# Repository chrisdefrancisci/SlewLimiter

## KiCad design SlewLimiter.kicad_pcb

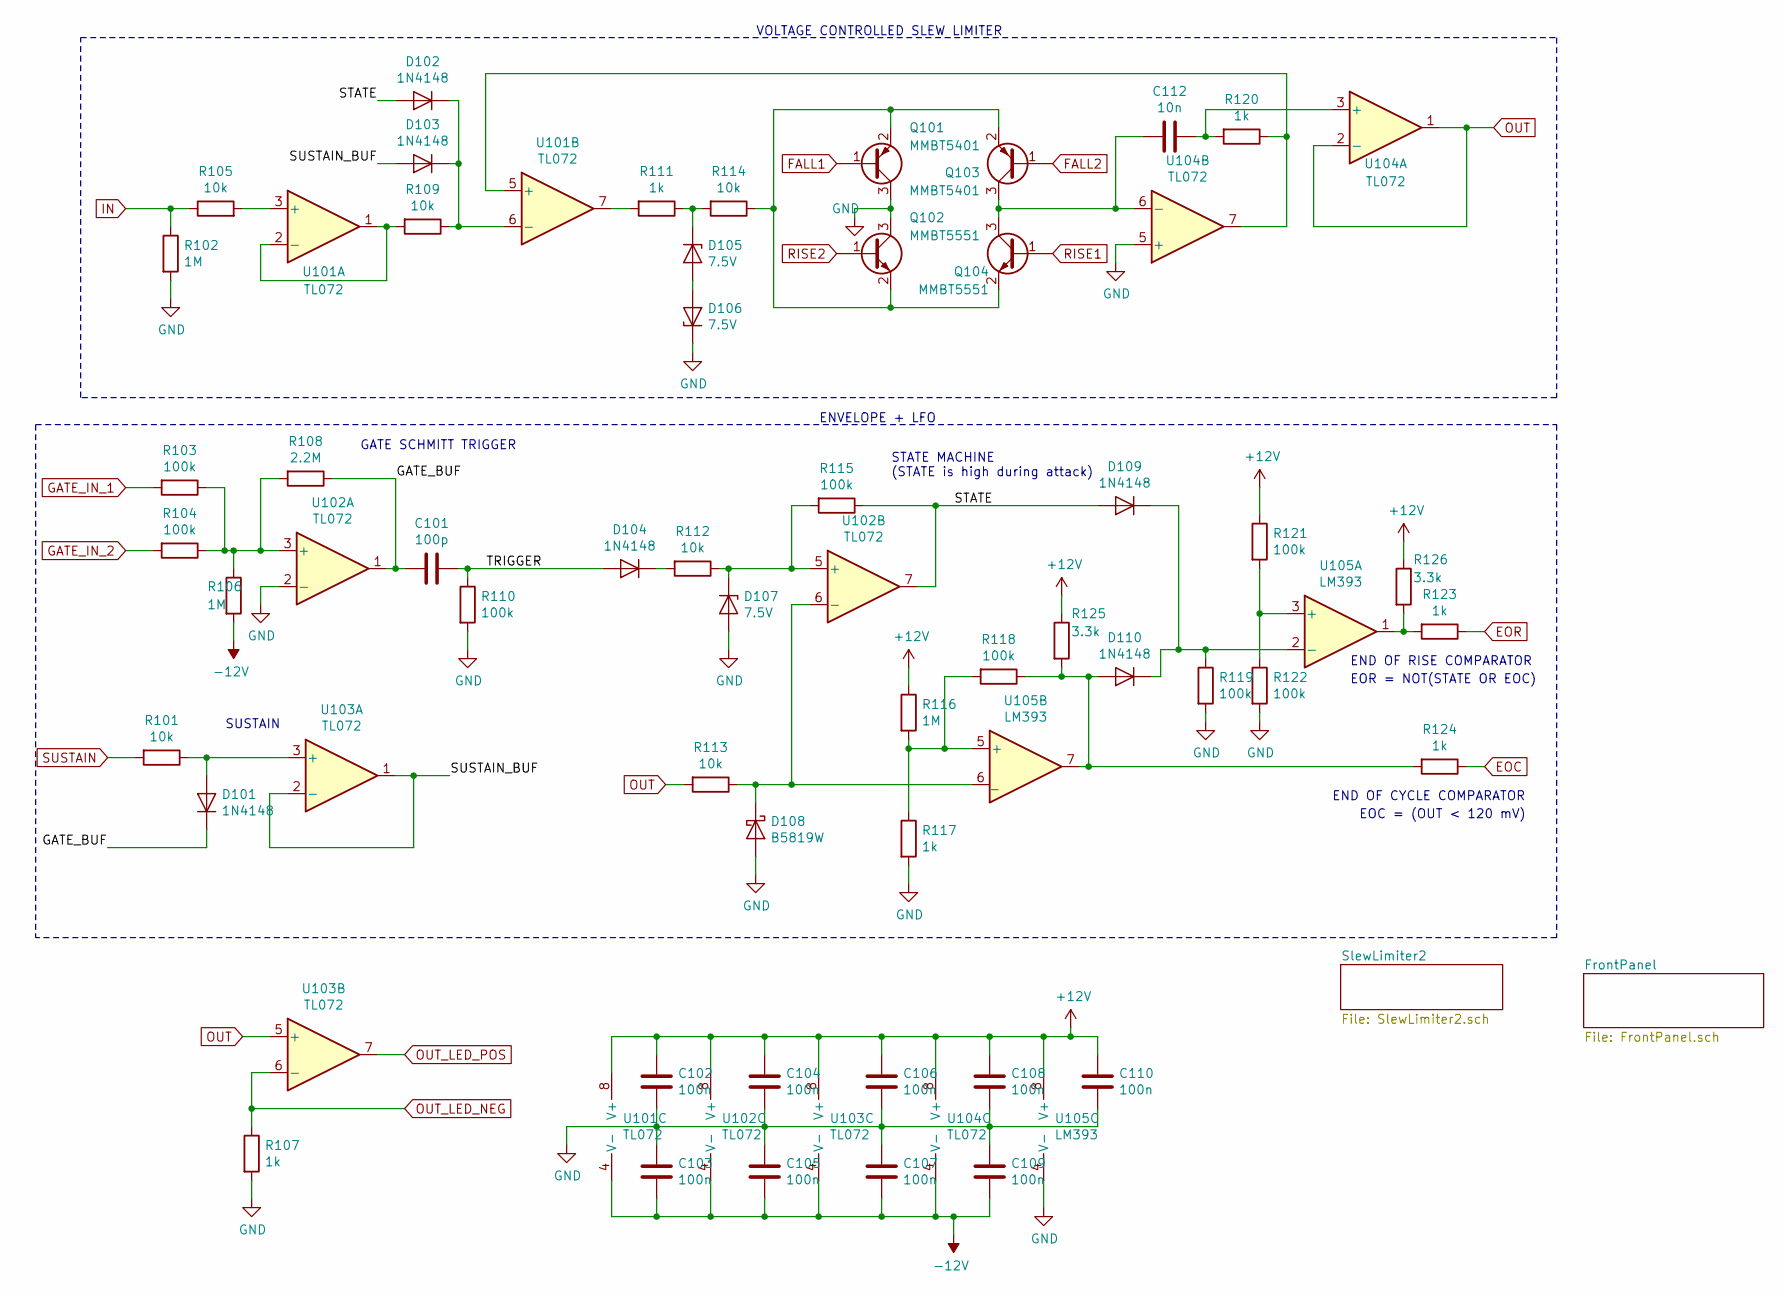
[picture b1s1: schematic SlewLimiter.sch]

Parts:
C101: 100p; C_0402_1005Metric; LCSC C1546
C102, C103, C104, C105, C106, C107, C108, C109, C110: 100n; C_0402_1005Metric; LCSC C1525
C112: 10n; C_0402_1005Metric; LCSC C15195
D101, D102, D103, D104, D109, D110: 1N4148; D_SOD-323F; LCSC C2128
D105, D106, D107: 7.5V; D_DO-35_SOD27_P7.62mm_Horizontal
D108: B5819W; D_SOD-123; LCSC C8598
Q101, Q103: MMBT5401; SOT-23; LCSC C8326
Q102, Q104: MMBT5551; SOT-23; LCSC C2145
R101, R105, R109, R112, R113, R114: 10k; R_0402_1005Metric; LCSC C25744
R102, R106, R116: 1M; R_0402_1005Metric; LCSC C26083
R103, R104, R110, R115, R118, R119, R121, R122: 100k; R_0402_1005Metric; LCSC C25741
R107, R111, R117, R120, R123, R124: 1k; R_0402_1005Metric; LCSC C11702
R108: 2.2M; R_0402_1005Metric; LCSC C11490
R125, R126: 3.3k; R_0402_1005Metric; LCSC C25890
U101, U102, U103, U104: TL072; SOIC-8_3.9x4.9mm_P1.27mm; LCSC C6961
U105: LM393; SOIC-8_3.9x4.9mm_P1.27mm; LCSC C7955

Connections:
+12V: C102.1, C104.1, C106.1, C108.1, C110.1, R116.1, R121.1, R125.1, R126.1, U101.8 (V+), U102.8 (V+), U103.8 (V+), U104.8 (V+), U105.8 (V+); also elsewhere on the board
-12V: C103.2, C105.2, C107.2, C109.2, R106.2, U101.4 (V-), U102.4 (V-), U103.4 (V-), U104.4 (V-); also elsewhere on the board
/GATE_BUF: C101.2, D101.1 (K), R108.1, U102.1
/STATE: D102.2 (A), D109.2 (A), R115.1, U102.7
/SUSTAIN_BUF: D103.2 (A), U103.1, U103.2 (-)
/TRIGGER: C101.1, D104.2 (A), R110.1
EOC: R124.1; also elsewhere on the board
EOR: R123.1; also elsewhere on the board
FALL1: Q101.1 (B); also elsewhere on the board
FALL2: Q103.1 (B); also elsewhere on the board
GATE_IN_1: R103.2; also elsewhere on the board
GATE_IN_2: R104.2; also elsewhere on the board
GND: C102.2, C103.1, C104.2, C105.1, C106.2, C107.1, C108.2, C109.1, C110.2, D106.1 (K), D107.2 (A), D108.2 (A), Q101.3 (C), Q102.3 (C), R102.2, R107.2, R110.2, R117.2, R119.2, R122.2, U102.2 (-), U104.5 (+), U105.4 (V-); also elsewhere on the board
IN: R102.1, R105.1; also elsewhere on the board
unnamed: C112.1, R120.2, U104.3 (+)
unnamed: C112.2, Q103.3 (C), Q104.3 (C), U104.6 (-)
unnamed: D101.2 (A), R101.1, U103.3 (+)
unnamed: D102.1 (K), D103.1 (K), R109.1, U101.6 (-)
unnamed: D104.1 (K), R112.2
unnamed: D105.1 (K), R111.1, R114.2
unnamed: D105.2 (A), D106.2 (A)
unnamed: D107.1 (K), R112.1, R115.2, U102.5 (+)
unnamed: D108.1 (K), R113.1, U102.6 (-), U105.6 (_)
unnamed: D109.1 (K), D110.1 (K), R119.1, U105.2 (-)
unnamed: D110.2 (A), R118.1, R124.2, R125.2, U105.7
unnamed: Q101.2 (E), Q102.2 (E), Q103.2 (E), Q104.2 (E), R114.1
unnamed: R103.1, R104.1, R106.1, R108.2, U102.3 (+)
unnamed: R105.2, U101.3 (+)
unnamed: R109.2, U101.1, U101.2 (-)
unnamed: R111.2, U101.7
unnamed: R116.2, R117.1, R118.2, U105.5 (+)
unnamed: R120.1, U101.5 (+), U104.7
unnamed: R121.2, R122.1, U105.3 (+)
unnamed: R123.2, R126.2, U105.1
OUT: R113.2, U103.5 (+), U104.1, U104.2 (-); also elsewhere on the board
OUT_LED_NEG: R107.1, U103.6 (-); also elsewhere on the board
OUT_LED_POS: U103.7; also elsewhere on the board
RISE1: Q104.1 (B); also elsewhere on the board
RISE2: Q102.1 (B); also elsewhere on the board
SUSTAIN: R101.2; also elsewhere on the board

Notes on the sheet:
VOLTAGE CONTROLLED SLEW LIMITER
ENVELOPE + LFO
SUSTAIN
GATE SCHMITT TRIGGER
STATE MACHINE (STATE is high during attack)
END OF CYCLE COMPARATOR
END OF RISE COMPARATOR
EOC = (OUT < 120 mV)
EOR = NOT(STATE OR EOC)

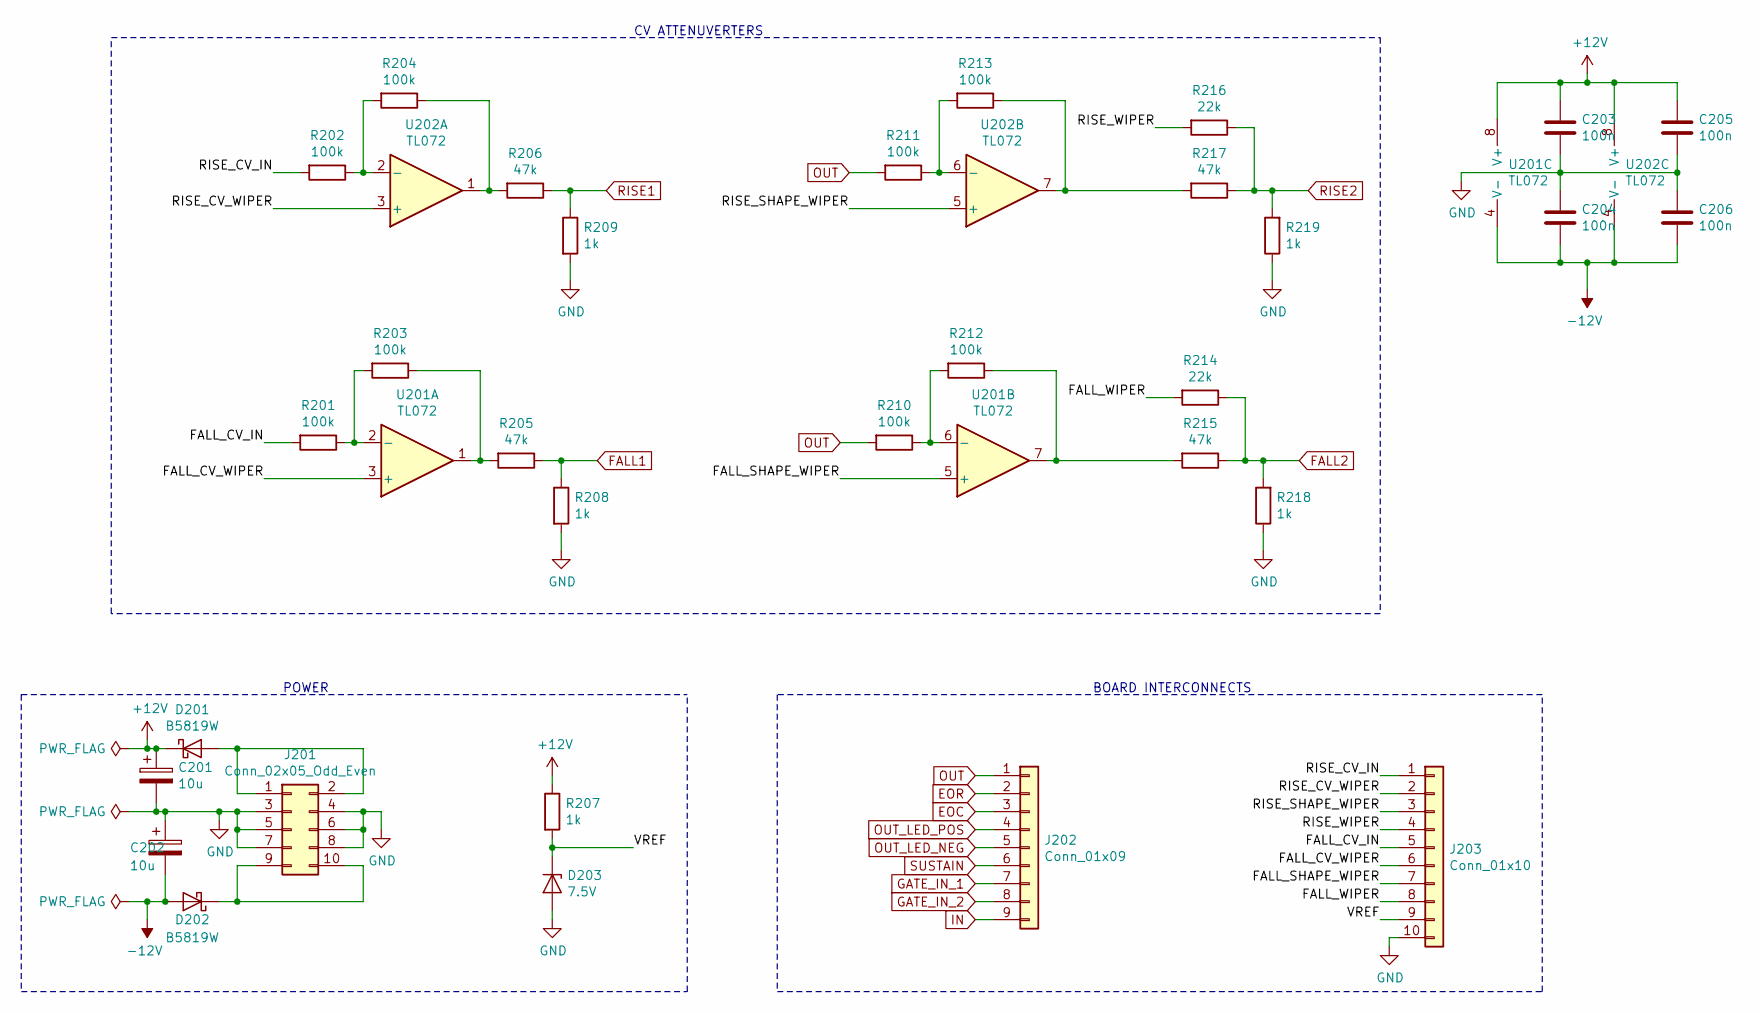
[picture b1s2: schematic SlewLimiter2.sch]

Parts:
C201, C202: 10u; C_0402_1005Metric; LCSC C15525
C203, C204, C205, C206: 100n; C_0402_1005Metric; LCSC C1525
D201, D202: B5819W; D_SOD-123; LCSC C8598
D203: 7.5V; D_DO-35_SOD27_P7.62mm_Horizontal
J201: Conn_02x05_Odd_Even; PinHeader_2x05_P2.54mm_Vertical
J202: Conn_01x09; PinHeader_1x09_P2.54mm_Vertical
J203: Conn_01x10; PinHeader_1x10_P2.54mm_Vertical
R201, R202, R203, R204, R210, R211, R212, R213: 100k; R_0402_1005Metric; LCSC C25741
R205, R206, R215, R217: 47k; R_0402_1005Metric; LCSC C25792
R207, R208, R209, R218, R219: 1k; R_0402_1005Metric; LCSC C11702
R214, R216: 22k; R_0402_1005Metric; LCSC C25768
U201, U202: TL072; SOIC-8_3.9x4.9mm_P1.27mm; LCSC C6961

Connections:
+12V: C201.1, C203.1, C205.1, D201.1 (K), R207.1, U201.8 (V+), U202.8 (V+); also elsewhere on the board
-12V: C202.2, C204.2, C206.2, D202.2 (A), U201.4 (V-), U202.4 (V-); also elsewhere on the board
/SlewLimiter2/FALL_CV_IN: J203.5, R201.2
/SlewLimiter2/FALL_CV_WIPER: J203.6, U201.3 (+)
/SlewLimiter2/FALL_SHAPE_WIPER: J203.7, U201.5 (+)
/SlewLimiter2/FALL_WIPER: J203.8, R214.2
/SlewLimiter2/RISE_CV_IN: J203.1, R202.2
/SlewLimiter2/RISE_CV_WIPER: J203.2, U202.3 (+)
/SlewLimiter2/RISE_SHAPE_WIPER: J203.3, U202.5 (+)
/SlewLimiter2/RISE_WIPER: J203.4, R216.2
/SlewLimiter2/VREF: D203.1 (K), J203.9, R207.2
EOC: J202.3; also elsewhere on the board
EOR: J202.2; also elsewhere on the board
FALL1: R205.1, R208.1; also elsewhere on the board
FALL2: R214.1, R215.1, R218.2; also elsewhere on the board
GATE_IN_1: J202.7; also elsewhere on the board
GATE_IN_2: J202.8; also elsewhere on the board
GND: C201.2, C202.1, C203.2, C204.1, C205.2, C206.1, D203.2 (A), J201.3, J201.4, J201.5, J201.6, J201.7, J201.8, J203.10, R208.2, R209.2, R218.1, R219.1; also elsewhere on the board
IN: J202.9; also elsewhere on the board
unnamed: D201.2 (A), J201.1, J201.2
unnamed: D202.1 (K), J201.9, J201.10
unnamed: R201.1, R203.2, U201.2 (-)
unnamed: R202.1, R204.2, U202.2 (-)
unnamed: R203.1, R205.2, U201.1
unnamed: R204.1, R206.2, U202.1
unnamed: R210.1, R212.2, U201.6 (-)
unnamed: R211.1, R213.2, U202.6 (-)
unnamed: R212.1, R215.2, U201.7
unnamed: R213.1, R217.2, U202.7
OUT: J202.1, R210.2, R211.2; also elsewhere on the board
OUT_LED_NEG: J202.5; also elsewhere on the board
OUT_LED_POS: J202.4; also elsewhere on the board
RISE1: R206.1, R209.1; also elsewhere on the board
RISE2: R216.1, R217.1, R219.2; also elsewhere on the board
SUSTAIN: J202.6; also elsewhere on the board

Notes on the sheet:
CV ATTENUVERTERS
POWER
BOARD INTERCONNECTS

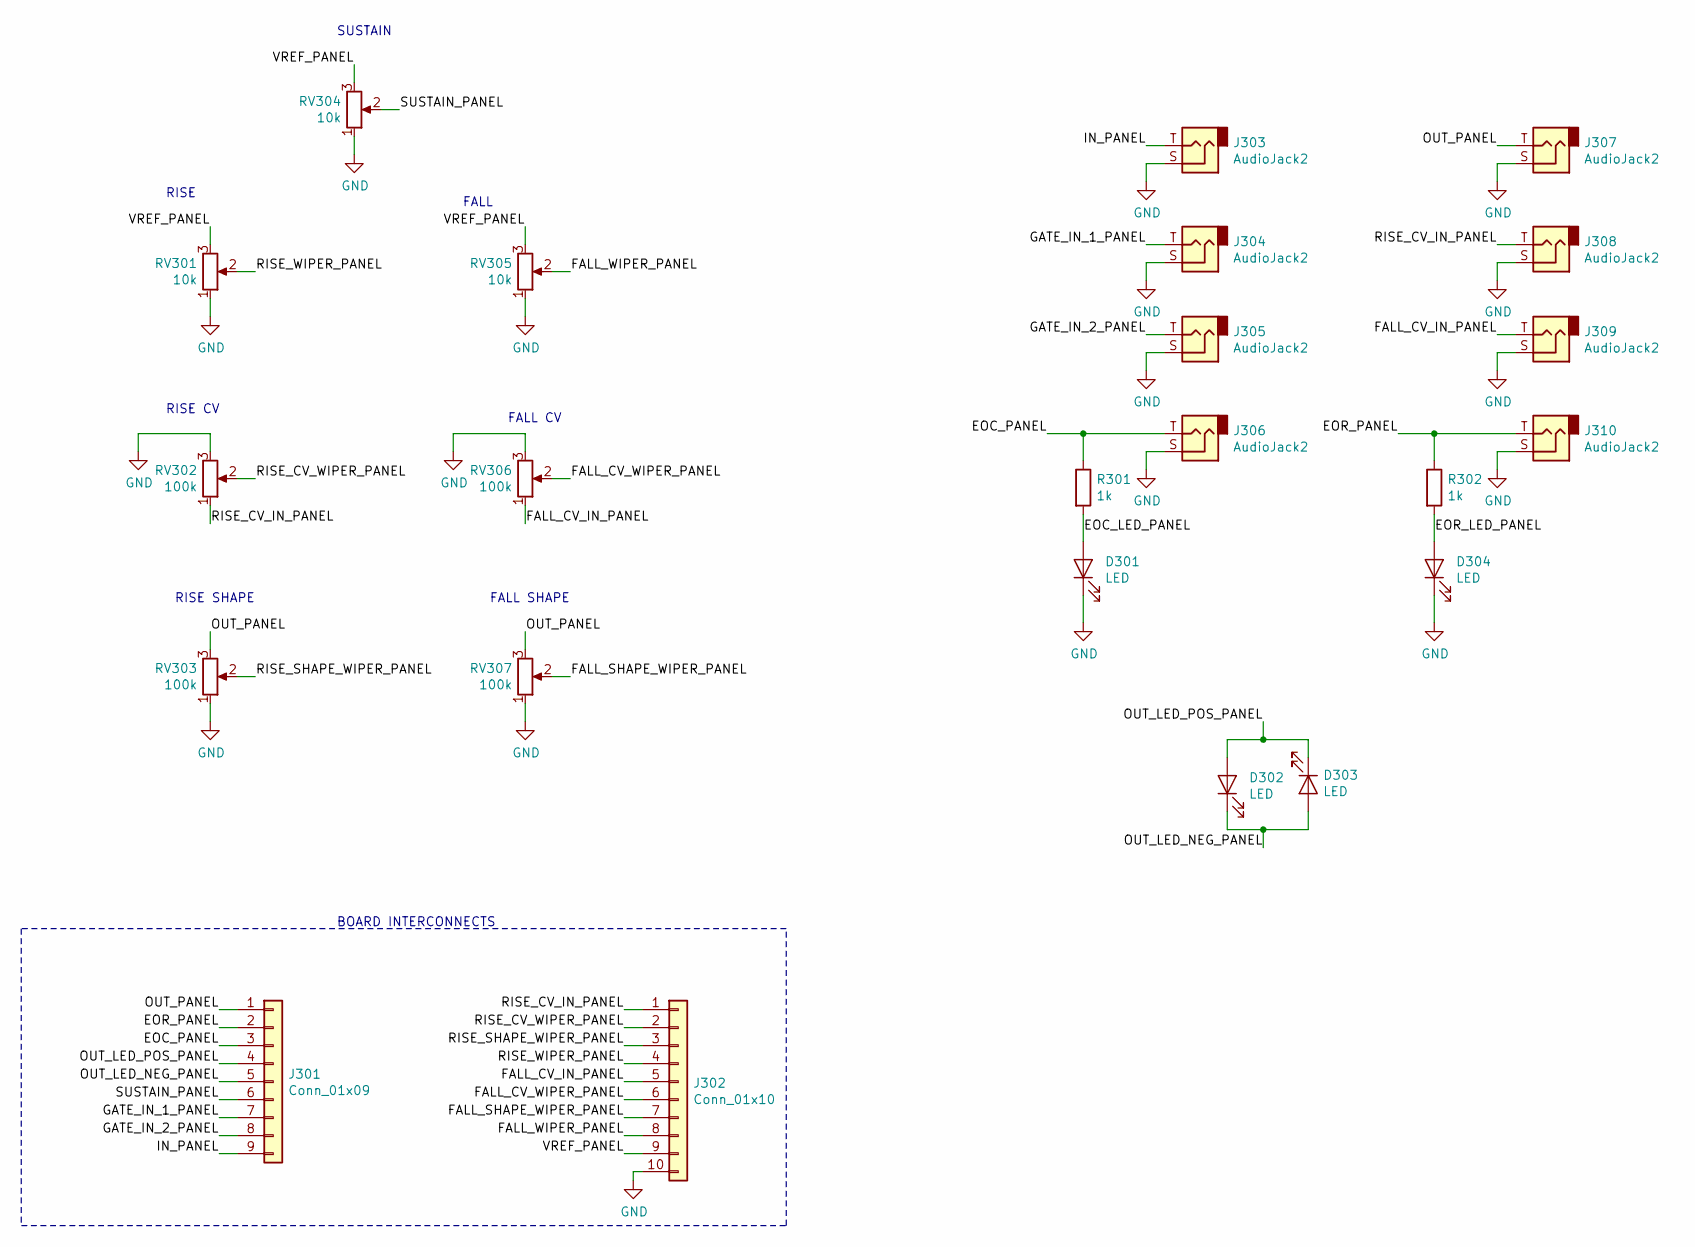
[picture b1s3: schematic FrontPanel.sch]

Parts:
D301, D302, D303, D304: LED; LED_D5.0mm
J301: Conn_01x09; PinSocket_1x09_P2.54mm_Vertical
J302: Conn_01x10; PinSocket_1x10_P2.54mm_Vertical
J303, J304, J305, J306, J307, J308, J309, J310: AudioJack2; A-2563
R301, R302: 1k; R_0402_1005Metric; LCSC C11702
RV301, RV304, RV305: 10k; A-5513
RV302, RV303, RV306, RV307: 100k; A-5513

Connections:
/FrontPanel/EOC_LED_PANEL: D301.2 (A), R301.2
/FrontPanel/EOC_PANEL: J301.3, J306.T, R301.1
/FrontPanel/EOR_LED_PANEL: D304.2 (A), R302.2
/FrontPanel/EOR_PANEL: J301.2, J310.T, R302.1
/FrontPanel/FALL_CV_IN_PANEL: J302.5, J309.T, RV306.1
/FrontPanel/FALL_CV_WIPER_PANEL: J302.6, RV306.2
/FrontPanel/FALL_SHAPE_WIPER_PANEL: J302.7, RV307.2
/FrontPanel/FALL_WIPER_PANEL: J302.8, RV305.2
/FrontPanel/GATE_IN_1_PANEL: J301.7, J304.T
/FrontPanel/GATE_IN_2_PANEL: J301.8, J305.T
/FrontPanel/IN_PANEL: J301.9, J303.T
/FrontPanel/OUT_LED_NEG_PANEL: D302.1 (K), D303.2 (A), J301.5
/FrontPanel/OUT_LED_POS_PANEL: D302.2 (A), D303.1 (K), J301.4
/FrontPanel/OUT_PANEL: J301.1, J307.T, RV303.3, RV307.3
/FrontPanel/RISE_CV_IN_PANEL: J302.1, J308.T, RV302.1
/FrontPanel/RISE_CV_WIPER_PANEL: J302.2, RV302.2
/FrontPanel/RISE_SHAPE_WIPER_PANEL: J302.3, RV303.2
/FrontPanel/RISE_WIPER_PANEL: J302.4, RV301.2
/FrontPanel/SUSTAIN_PANEL: J301.6, RV304.2
/FrontPanel/VREF_PANEL: J302.9, RV301.3, RV304.3, RV305.3
GND: D301.1 (K), D304.1 (K), J302.10, J303.S, J304.S, J305.S, J306.S, J307.S, J308.S, J309.S, J310.S, RV301.1, RV302.3, RV303.1, RV304.1, RV305.1, RV306.3, RV307.1; also elsewhere on the board

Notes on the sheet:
BOARD INTERCONNECTS
SUSTAIN
RISE
FALL
RISE CV
FALL CV
RISE SHAPE
FALL SHAPE

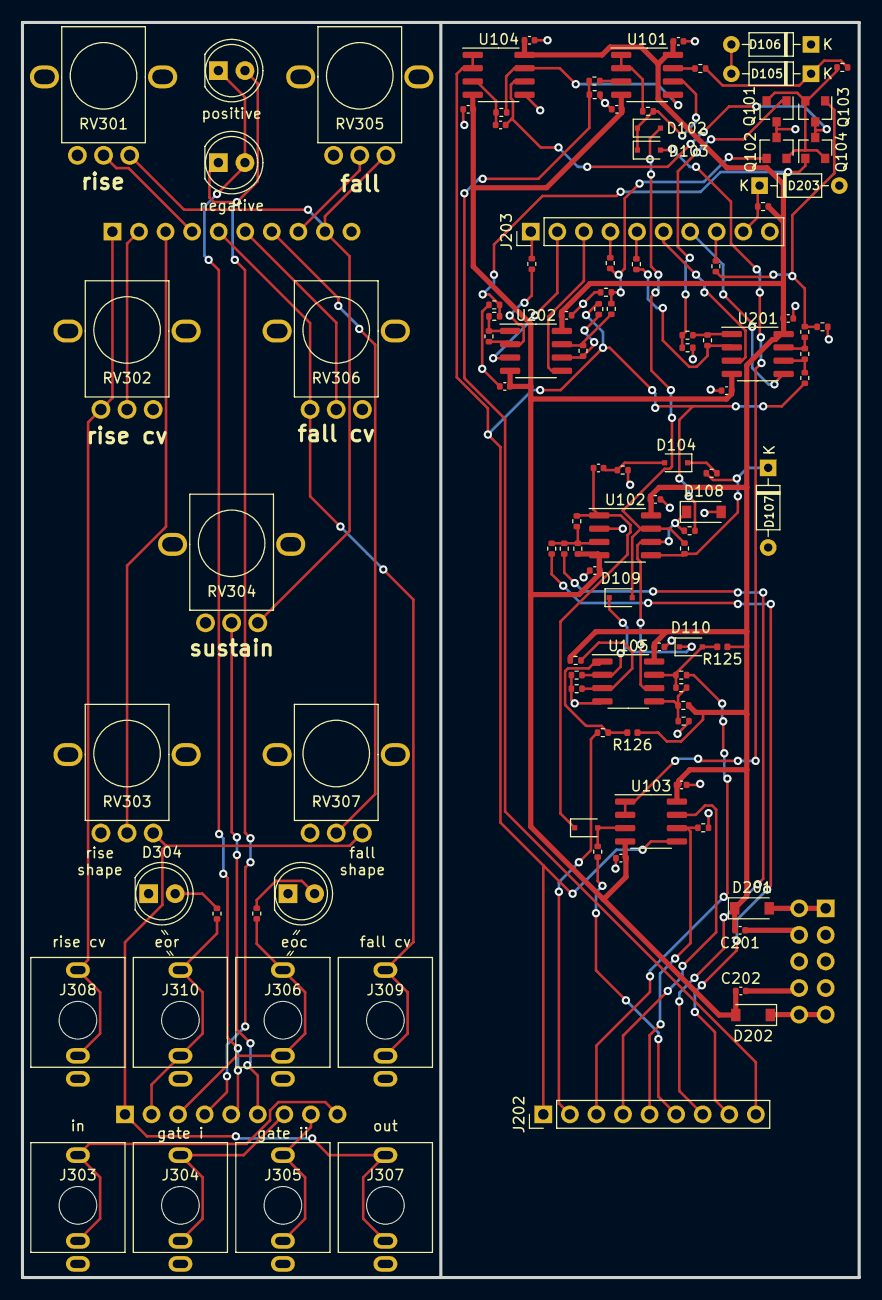
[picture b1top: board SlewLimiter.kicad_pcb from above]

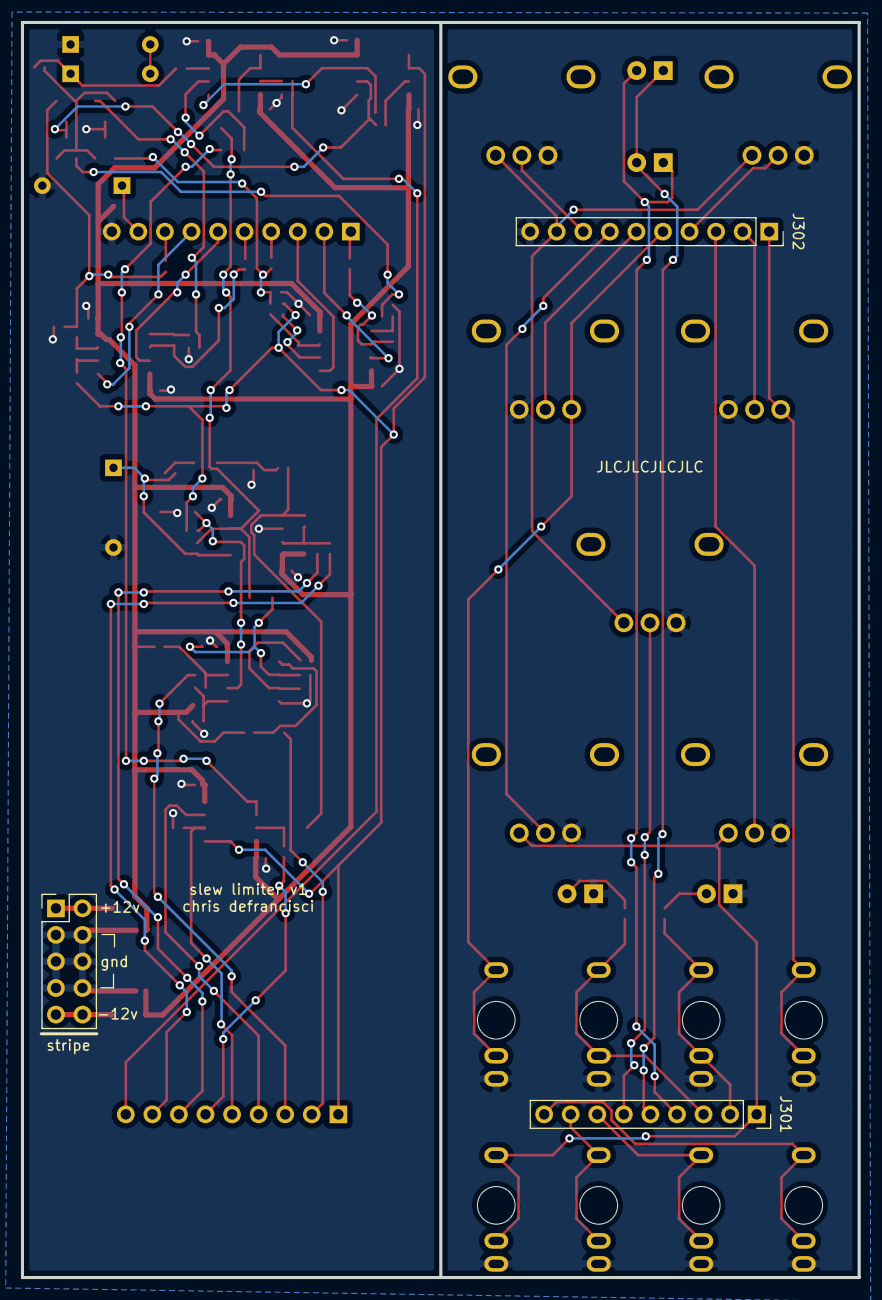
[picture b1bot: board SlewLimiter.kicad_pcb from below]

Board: 2 copper layers, 80.0 x 120.0 mm, 112 parts (3 on the bottom side), 79 nets.

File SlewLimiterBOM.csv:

Comment,Designator,Footprint,LCSC
"100p","C101","Capacitor_SMD:C_0402_1005Metric","C1546"
"100n","C102,C103,C104,C105,C106,C107,C108,C109,C110,C203,C204,C205,C206","Capacitor_SMD:C_0402_1005Metric","C1525"
"10n","C112","Capacitor_SMD:C_0402_1005Metric","C15195"
"10u","C201,C202","Capacitor_SMD:C_0402_1005Metric","C15525"
"1N4148","D101,D102,D103,D104,D109,D110","Diode_SMD:D_SOD-323F","C2128"
"7.5V","D105,D106,D107,D203","Diode_THT:D_DO-35_SOD27_P7.62mm_Horizontal",""
"B5819W","D108,D201,D202","Diode_SMD:D_SOD-123","C8598"
"LED","D301,D302,D303,D304","LED_THT:LED_D5.0mm",""
"Conn_02x05_Odd_Even","J201","Connector_PinHeader_2.54mm:PinHeader_2x05_P2.54mm_Vertical",""
"Conn_01x09","J202","Connector_PinHeader_2.54mm:PinHeader_1x09_P2.54mm_Vertical",""
"Conn_01x10","J203","Connector_PinHeader_2.54mm:PinHeader_1x10_P2.54mm_Vertical",""
"Conn_01x09","J301","Connector_PinSocket_2.54mm:PinSocket_1x09_P2.54mm_Vertical",""
"Conn_01x10","J302","Connector_PinSocket_2.54mm:PinSocket_1x10_P2.54mm_Vertical",""
"AudioJack2","J303,J304,J305,J306,J307,J308,J309,J310","A-2563:A-2563",""
"MMBT5401","Q101,Q103","Package_TO_SOT_SMD:SOT-23","C8326"
"MMBT5551","Q102,Q104","Package_TO_SOT_SMD:SOT-23","C2145"
"1M","R102,R106,R116","Resistor_SMD:R_0402_1005Metric","C26083"
"100k","R103,R104,R110,R115,R118,R119,R121,R122,R201,R202,R203,R204,R210,R211,R212,R213","Resistor_SMD:R_0402_1005Metric","C25741"
"10k","R101,R105,R109,R112,R113,R114","Resistor_SMD:R_0402_1005Metric","C25744"
"2.2M","R108","Resistor_SMD:R_0402_1005Metric","C11490"
"1k","R107,R111,R117,R120,R123,R124,R207,R208,R209,R218,R219,R301,R302","Resistor_SMD:R_0402_1005Metric","C11702"
"47k","R205,R206,R215,R217","Resistor_SMD:R_0402_1005Metric","C25792"
"22k","R214,R216","Resistor_SMD:R_0402_1005Metric","C25768"
"10k","RV301,RV304,RV305","A-5513:A-5513",""
"100k","RV302,RV303,RV306,RV307","A-5513:A-5513",""
"TL072","U101,U102,U103,U104,U201,U202","Package_SO:SOIC-8_3.9x4.9mm_P1.27mm","C6961"
"LM393","U105","Package_SO:SOIC-8_3.9x4.9mm_P1.27mm","C7955"

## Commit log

2021-05-24 Finished schematic - some confusion on comparator
2021-05-24 Labelled all component values
2021-10-13 Branch to document 2nd order of boards
2021-10-13 Changed EOC + terminal to go to gnd instead of -12v, added 3.3k pullup resistors to lm393 outputs
2021-10-17 Routed board with updated changes - pullup resistors on comparators, input to U105B goes to GND instead of -12V
